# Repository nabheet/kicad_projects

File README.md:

# kicad_projects
Respository of personal KiCad projects that I have developed for home use. I am a Software Engineer by professional choice. Due to my professional commitments, like a lot of us, I am required to learn something new every few months. After recovering from the craziness and disruption created by COVID, I felt like I needed to learn something new. I felt like I needed to pick something other than software to learn. Golf feels like a pointless exercise in personal vanity, so here I am. I have been learning PCB schematic and layout design for fun since 2023.  I am sharing these with the world so we can all learn together.

These are actual working schematics as I have had them manufactured by [PCB Way](https://www.pcbway.com/). I have a few boards already printed and soldered them myself. I am willing to sell them for a mutually acceptable price. However, there are no implied guarantees and warrantees. Their usage will be at your own risk as this is a personal hobby project. I only need some time to solder all the components on to the board.

I can share working videos as needed.

# Project List

## Blind Controller
This project uses an ESP32-C3 to control a [DRV8874 H-bridge motor driver](https://www.ti.com/product/DRV8874) for controlling blinds. I have an outdoor blind which is quite hard to roll up and down. So the specs for the motor needed to be pretty high. I ended up using a [12v 40RPM motor](https://a.co/d/eGuKaqe) with a rated torque of 40kgcm.

I came up with the torque numbers by tying a bucket with a paracord to the blind cord. I slowly added water to the bucket until the blind rotated. Weighing the bucket and water gave me minimum weight needed to move the blind, which I then converted to force/torque. I do not remember the actual numbers but this gave me enough to buy this motor with enough buffer. IIRC, I think I went with double the calculated value.

In the previous iterations of this design I had an AC/DC converter on the board. The output current ratings for these converters was not enough for my needs. I needed at least 5A max current to prevent motor stall. And they were really bulky to mount on the board. So I decided to use an external 12v/6A power supply with barrel jack plug. The 12v is converted to 3.3v using [AP62250WU](https://www.diodes.com/assets/Datasheets/AP62250.pdf) buck converter to power the ESP32-C3.

This ESP32-C3 chip is then flashed with [ESPHome](https://esphome.io/) and integrated with [Home Assistant](https://www.home-assistant.io/). Or it is ready for your programming desires.

### Warnings:
1. Even though the components are rated for 5A, the track from the motor driver to the barrel jack connector is the default width (~9mils). My google search seems to show that ~10mils is good for ~2A. So it is probably not a good idea to run sustained loads of high amperage through this track.

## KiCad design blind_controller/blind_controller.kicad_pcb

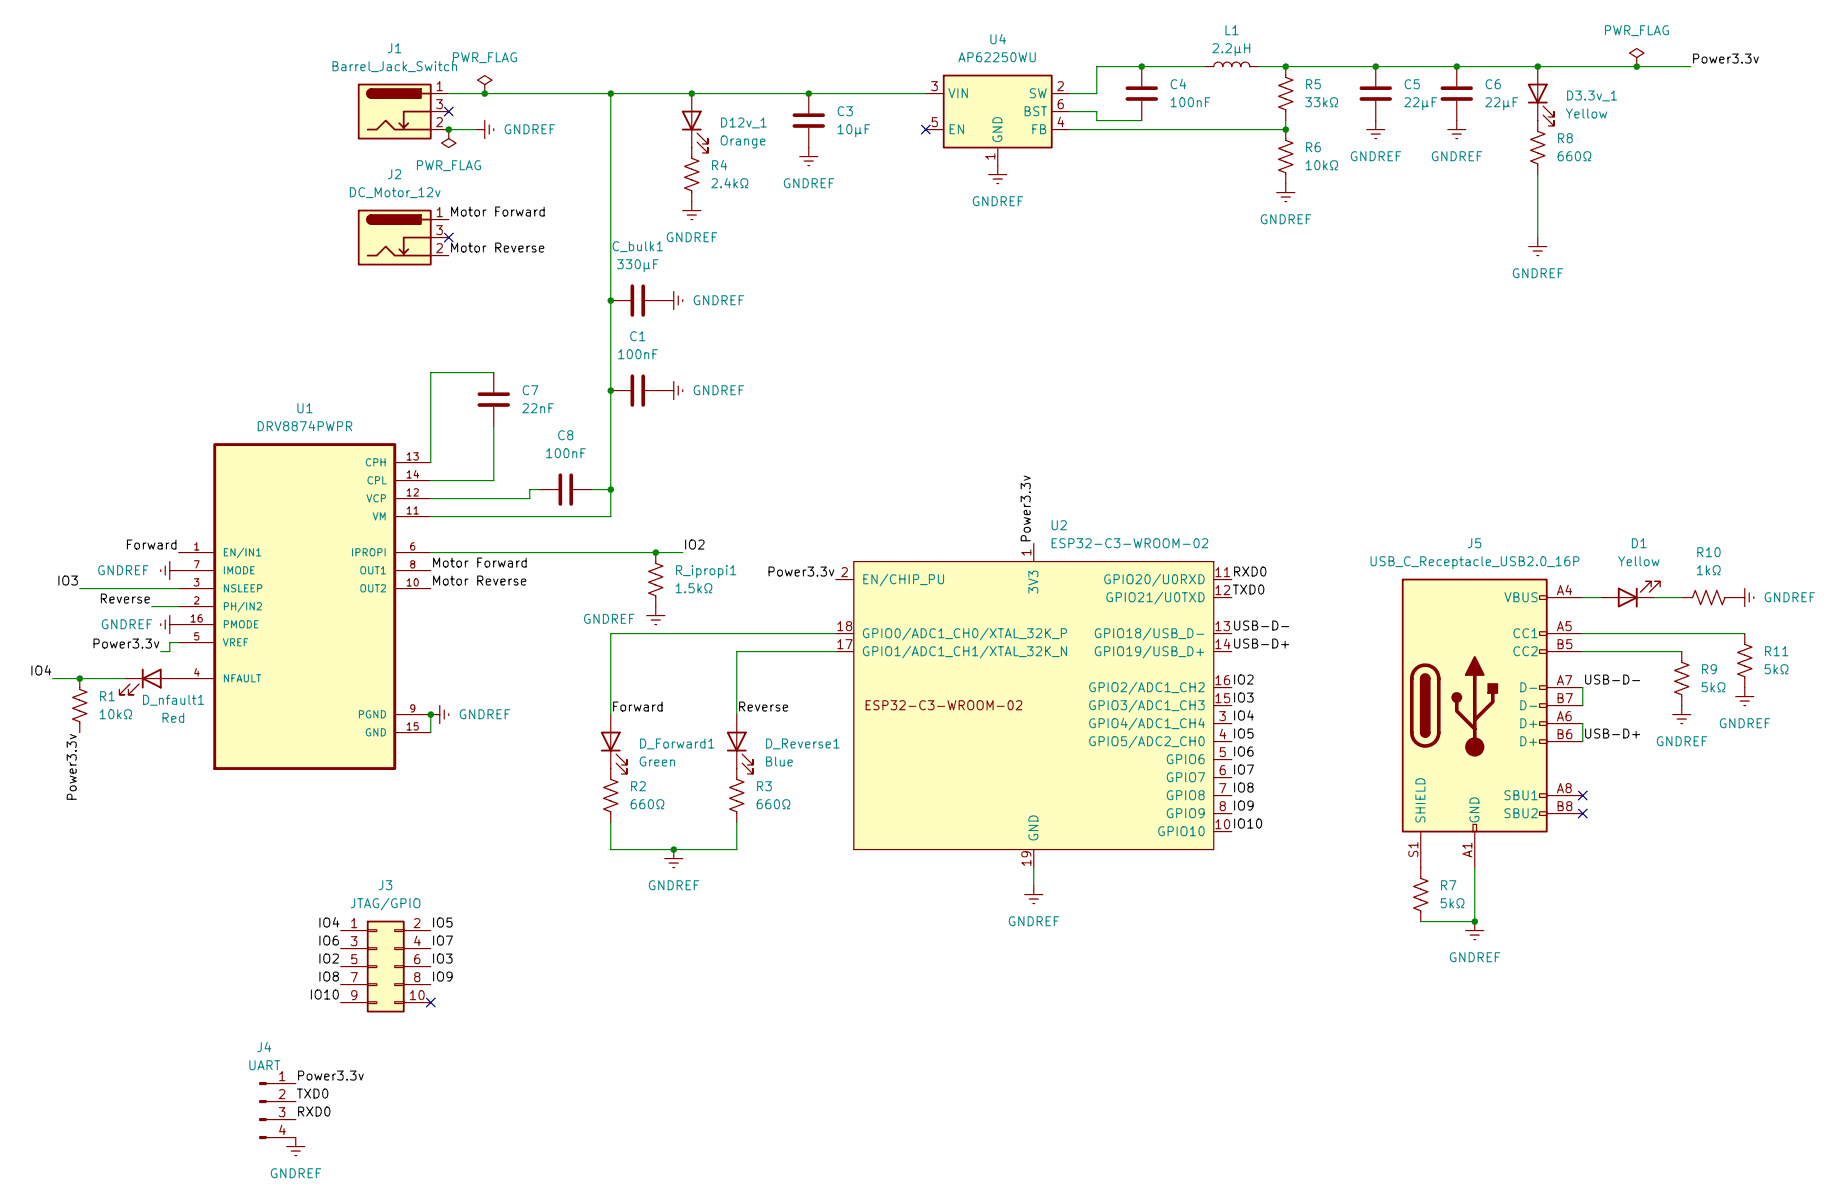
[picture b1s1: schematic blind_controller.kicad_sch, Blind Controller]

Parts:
C1, C4, C8: 100nF; C_1206_3216Metric_Pad1.33x1.80mm_HandSolder
C3: 10µF; C_1206_3216Metric_Pad1.33x1.80mm_HandSolder
C5, C6: 22µF; C_1206_3216Metric_Pad1.33x1.80mm_HandSolder
C7: 22nF; C_1206_3216Metric_Pad1.33x1.80mm_HandSolder
C_bulk1: 330µF; CP_Radial_D8.0mm_P2.50mm
D1, D3.3v_1: Yellow; LED_1206_3216Metric_Pad1.42x1.75mm_HandSolder
D12v_1: Orange; LED_1206_3216Metric_Pad1.42x1.75mm_HandSolder
D_Forward1: Green; LED_1206_3216Metric_Pad1.42x1.75mm_HandSolder
D_Reverse1: Blue; LED_1206_3216Metric_Pad1.42x1.75mm_HandSolder
D_nfault1: Red; LED_1206_3216Metric_Pad1.42x1.75mm_HandSolder
J1: Barrel_Jack_Switch; BarrelJack_Horizontal
J2: DC_Motor_12v; BarrelJack_Horizontal
J3: JTAG/GPIO; PinHeader_2x05_P2.54mm_Vertical
J4: UART; PinHeader_1x04_P2.54mm_Vertical
J5: USB_C_Receptacle_USB2.0_16P; USB_C_Receptacle_GCT_USB4085
L1: 2.2µH; L_Radial_D7.5mm_P5.00mm_Fastron_07P
R1, R6: 10kΩ; R_1206_3216Metric_Pad1.30x1.75mm_HandSolder
R2, R3, R8: 660Ω; R_1206_3216Metric_Pad1.30x1.75mm_HandSolder
R4: 2.4kΩ; R_1206_3216Metric_Pad1.30x1.75mm_HandSolder
R5: 33kΩ; R_1206_3216Metric_Pad1.30x1.75mm_HandSolder
R7, R9, R11: 5kΩ; R_1206_3216Metric_Pad1.30x1.75mm_HandSolder
R10: 1kΩ; R_1206_3216Metric_Pad1.30x1.75mm_HandSolder
R_ipropi1: 1.5kΩ; R_1206_3216Metric_Pad1.30x1.75mm_HandSolder
U1: DRV8874PWPR; SOP65P640X120-17N
U2: ESP32-C3-WROOM-02
U4: AP62250WU; TSOT-23-6_HandSoldering

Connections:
/Forward: D_Forward1.2 (A), U1.1 (EN/IN1), U2.18 (GPIO0/ADC1_CH0/XTAL_32K_P)
/IO2: J3.5, R_ipropi1.1, U1.6 (IPROPI), U2.16 (GPIO2/ADC1_CH2)
/IO3: J3.6, U1.3 (NSLEEP), U2.15 (GPIO3/ADC1_CH3)
/IO4: D_nfault1.1 (K), J3.1, R1.1, U2.3 (GPIO4/ADC1_CH4)
/IO5: J3.2, U2.4 (GPIO5/ADC2_CH0)
/IO6: J3.3, U2.5 (GPIO6)
/IO7: J3.4, U2.6 (GPIO7)
/IO8: J3.7, U2.7 (GPIO8)
/IO9: J3.8, U2.8 (GPIO9)
/IO10: J3.9, U2.10 (GPIO10)
/Motor Forward: J2.1, U1.8 (OUT1)
/Motor Reverse: J2.2, U1.10 (OUT2)
/Power3.3v: C5.1, C6.1, D3.3v_1.2 (A), J4.1, L1.2, R1.2, R5.1, U1.5 (VREF), U2.1 (3V3), U2.2 (EN/CHIP_PU)
/RXD0: J4.3, U2.11 (GPIO20/U0RXD)
/Reverse: D_Reverse1.2 (A), U1.2 (PH/IN2), U2.17 (GPIO1/ADC1_CH1/XTAL_32K_N)
/TXD0: J4.2, U2.12 (GPIO21/U0TXD)
/USB-D+: J5.A6 (D+), J5.B6 (D+), U2.14 (GPIO19/USB_D+)
/USB-D-: J5.A7 (D-), J5.B7 (D-), U2.13 (GPIO18/USB_D-)
GNDREF: C1.2, C3.2, C5.2, C6.2, C_bulk1.2, J1.2, J4.4, J5.A1 (GND), J5.A12 (GND), J5.B1 (GND), J5.B12 (GND), R2.2, R3.2, R4.2, R6.2, R7.2, R8.2, R9.2, R10.2, R11.2, R_ipropi1.2, U1.7 (IMODE), U1.9 (PGND), U1.15 (GND), U1.16 (PMODE), U1.17, U2.9 (GND), U2.19 (GND), U4.1 (GND)
unnamed: D1.2 (A), J5.A4 (VBUS), J5.A9 (VBUS), J5.B4 (VBUS), J5.B9 (VBUS)
unnamed: D1.1 (K), R10.1
unnamed: D3.3v_1.1 (K), R8.1
unnamed: C1.1, C3.1, C8.2, C_bulk1.1, D12v_1.2 (A), J1.1, U1.11 (VM), U4.3 (VIN)
unnamed: D12v_1.1 (K), R4.1
unnamed: D_Forward1.1 (K), R2.1
unnamed: D_Reverse1.1 (K), R3.1
unnamed: D_nfault1.2 (A), U1.4 (NFAULT)
unnamed: J5.A5 (CC1), R11.1
unnamed: J5.B5 (CC2), R9.1
unnamed: J5.S1 (SHIELD), R7.1
unnamed: C7.1, U1.13 (CPH)
unnamed: C7.2, U1.14 (CPL)
unnamed: C8.1, U1.12 (VCP)
unnamed: C4.2, U4.6 (BST)
unnamed: R5.2, R6.1, U4.4 (FB)
unnamed: C4.1, L1.1, U4.2 (SW)

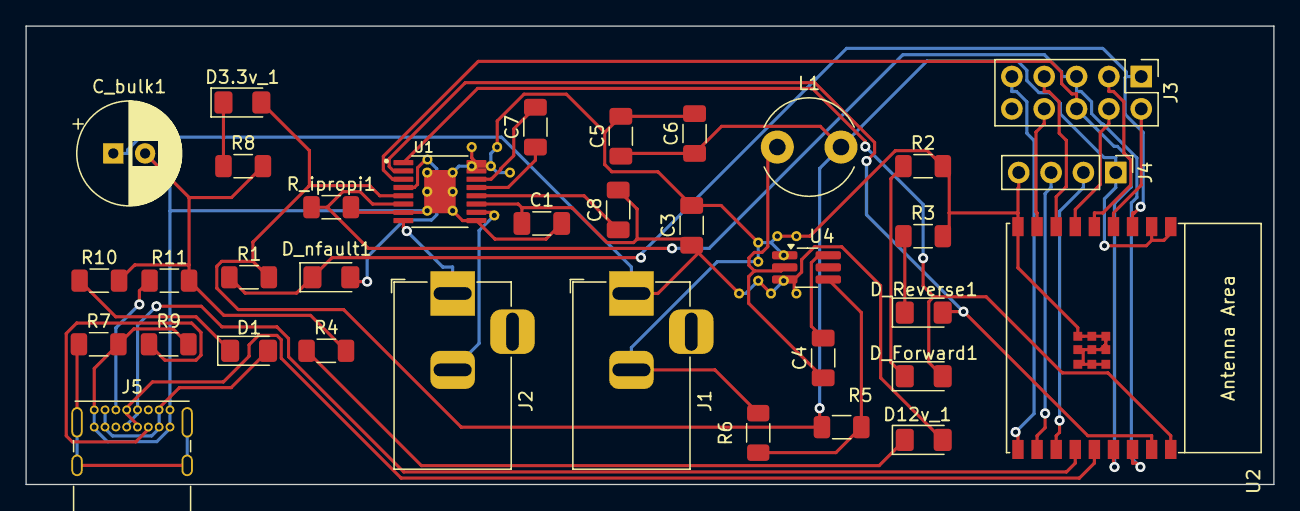
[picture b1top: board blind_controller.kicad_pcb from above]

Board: 2 copper layers, 98.0 x 36.0 mm, 35 parts (0 on the bottom side), 36 nets.

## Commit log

2024-12-01 add GPLv3 and CERN-OHLv2 license
2024-12-01 add GPLv3 and CERN-OHLv2 license (#1)
2024-12-01 Add schematic and layout for blind motor controller. Also add some more extensions to ignore.
2024-12-01 add project description to readme
2024-12-02 add current limit warning and ESP32-C3 info
2024-12-02 Add schematic and layout for blind motor controller (#2)
    * Add schematic and layout for blind motor controller. Also add some more extensions to ignore.
    * add project description to readme
    * add current limit warning and ESP32-C3 info
